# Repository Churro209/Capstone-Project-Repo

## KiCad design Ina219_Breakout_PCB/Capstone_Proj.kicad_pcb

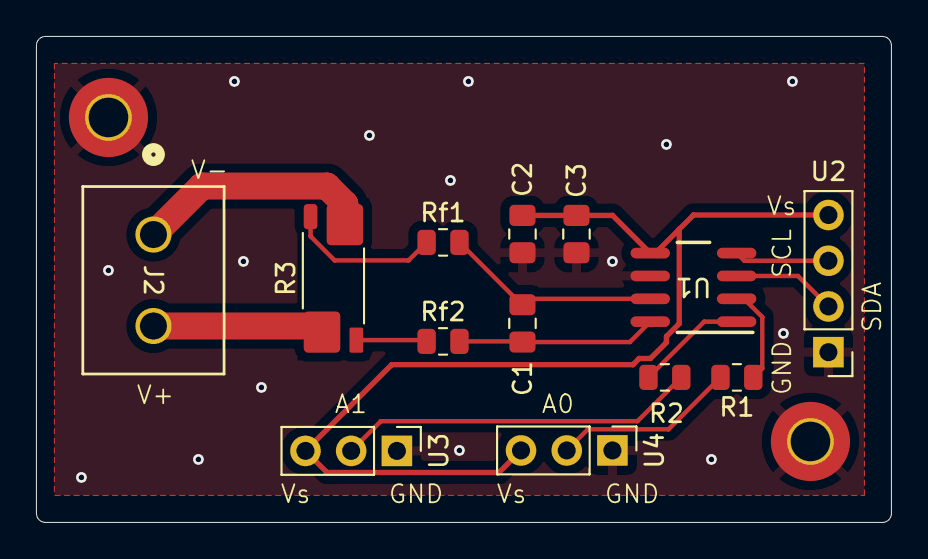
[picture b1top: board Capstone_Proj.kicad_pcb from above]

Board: 2 copper layers, 47.5 x 27.0 mm, 13 parts (0 on the bottom side), 14 nets.

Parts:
C1, C3: .1µF; C_0805_2012Metric_Pad1.18x1.45mm_HandSolder
C2: 10µF; C_0805_2012Metric_Pad1.18x1.45mm_HandSolder
J2: Screw_Terminal_01x02; CONN_MBES-152_ALT
R1, R2: 0; R_0805_2012Metric
R3: R_Shunt; R_Shunt_Vishay_WSK2512_6332Metric_T1.19mm
Rf1, Rf2: 10Ω; R_0805_2012Metric
U1: INA219AIDR; D0008A_N
U2: 455-1706-ND; PinHeader_1x04_P2.54mm_Vertical
U3, U4: 455-1705-ND; PinHeader_1x03_P2.54mm_Vertical

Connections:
/I2C_SCL: U1.4 (SCL), U2.3
/I2C_SDA: U1.3 (SDA), U2.2
GND: C2.1, C3.1, U1.6 (GND), U2.1, U3.1, U4.1
unnamed: J2.1, R3.4
unnamed: J2.2, R3.1
unnamed: R1.2, U4.2
unnamed: R2.2, U3.2
unnamed: R3.2, Rf2.1
unnamed: R3.3, Rf1.1
unnamed: R1.1, U1.2 (A0)
unnamed: R2.1, U1.1 (A1)
unnamed: C1.1, Rf2.2, U1.8 (VIN+)
unnamed: C1.2, Rf1.2, U1.7 (VIN-)
unnamed: C2.2, C3.2, U1.5 (VS), U2.4, U3.3, U4.3

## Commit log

2026-01-07 intial commit for files to share
2026-01-07 Ignore Lab notebook template
2026-01-10 1/09/2026 lab entry. Soldered INA219 Breakout PCB and verified continuity and no shorts.
2026-01-10 Remove png from ignore list. See if that makes photo populate correctly in pdf
2026-01-10 01/09/2026 Lab Entry: Soldered INA219 breakout PCB. Used a multimeter to test for solid connections and shorts. PASSED.
2026-01-10 remove photo and add it back to .gitignore
2026-01-10 ignore photos
2026-01-12 1/11/2026 INA219 PCB ACK HIL test: PASSED
2026-01-15 INA219-HIL-TEST: write and read registers. PASSED
2026-01-18 INA219 Board 2: HIL test. PASSED
2026-01-25 Research: Gate Drive IC Data sheet & PWM Generation on Raspberry Pi Pico.
2026-01-31 Verify equations and parameter values to generate correct PWM. Use this file when writing the .c file
2026-02-01 Verified functionality of PWM with HIL/SIL tests
2026-02-09 IR2101PBF -HIL test. Repeat with Low side mosfet and smaller load value.
2026-02-12 Proof of concept to prevent shoot through on synchronous buck converter.
2026-02-12 Proof Of concept for PWM high and low side config with shoot through prevention.
2026-02-14 Test gate drive with high and low side mosfets. Will not use.
2026-02-21 HIL test Buck Converter + PWM from Pico + Gate Drive IC. No Feed back
2026-02-21 PCB Re Design
2026-02-27 remove pdf and allow .md files. Also determine Rsense and some other calculations for INA240
2026-02-27 test to see if this fixes image generation
2026-03-01 PCB layout
